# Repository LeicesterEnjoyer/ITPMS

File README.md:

# ITPMS

## A lightweight, energy-efficient **Improved TPMS with integrated tire wear assistant (ITPMS)**. Designed for universal compatibility and precision.

## 🔥 Key Features

- **🏋️ Ultra-Compact Design**  
    Minimal weight (<30g) ensures compatibility with most tires without affecting balance.

- **📡 Autonomous Operation**  
    Wakes up via accelerometer motion detection → close to none battery drain when stationary.

- **📊 Fast And Precise**  
    Uses device computing from sensors such as:
    - Pressure sensor
    - Temperature sensor (built into the MCU)
    - 3-axis accelerometer
    - Hall effect sensor

- **🔋 10-Year Battery Life**  
    Has low-powered elements and works only while the vehicle is moving.

- **🎯 Hall Effect Initialization**  
    Quick pairing with magnetic TPMS initializing pen.

## 🛠 How It Works

### Installation & Activation

1. **Open** remove the tire from the rim.
2. **Mount** the TPMs on the stem valve inside the tire .
3. **Wake & Pair** the TPMs with the magnetic TPMS initializing pen.
4. **Drive** to see the real time pressure and temperature changes.

### Data Transmission

| Trigger                                   | Action                         |
|-------------------------------------------|--------------------------------|
| > 5% pressure deviation from last read    | Instant RF alert to ECU        |
| > 5% temperature deviation from last read | Instant RF alert to ECU        |
| 10s without any significant changes       | Keep-alive ping                |

## 🔍 Code library

ITPMS/  
├── [Assistant/](Assistant/)&nbsp;&nbsp;&nbsp;&nbsp;&nbsp;&nbsp;&nbsp;&nbsp;&nbsp;&nbsp;&nbsp;&nbsp;&nbsp;&nbsp;&nbsp;&nbsp;&nbsp;&nbsp;&nbsp;&nbsp;&nbsp;&nbsp;&nbsp;&nbsp;&nbsp;&nbsp;&nbsp;&nbsp;&nbsp;&nbsp;&nbsp;&nbsp;# All files for the tire wear assistant.  
│&nbsp;&nbsp;&nbsp;├── [assets/](Assistant/assets/)&nbsp;&nbsp;&nbsp;&nbsp;&nbsp;&nbsp;&nbsp;&nbsp;&nbsp;&nbsp;&nbsp;&nbsp;&nbsp;&nbsp;&nbsp;&nbsp;&nbsp;&nbsp;&nbsp;&nbsp;&nbsp;&nbsp;&nbsp;&nbsp;&nbsp;&nbsp;&nbsp;&nbsp;&nbsp;&nbsp;&nbsp;# Assets for the UI.  
│&nbsp;&nbsp;&nbsp;├── [CSVhandling/](Assistant/CSVhandling/)  
│&nbsp;&nbsp;&nbsp;│&nbsp;&nbsp;&nbsp;&nbsp;|── [CSVmanager.py](Assistant/CSVhandling/CSVmanager.py)&nbsp;&nbsp;&nbsp;&nbsp;&nbsp;&nbsp;&nbsp;&nbsp;&nbsp;&nbsp;&nbsp;&nbsp;# Read and write operations for csv files.  
│&nbsp;&nbsp;&nbsp;│&nbsp;&nbsp;&nbsp;└── [DataGenerator.py](Assistant/CSVhandling/DataGenerator.py)&nbsp;&nbsp;&nbsp;&nbsp;&nbsp;&nbsp;&nbsp;&nbsp;# Generator for (TPMs) tire data.  
│&nbsp;&nbsp;&nbsp;│  
│&nbsp;&nbsp;&nbsp;├── [Data/](Assistant/Data/)&nbsp;&nbsp;&nbsp;&nbsp;&nbsp;&nbsp;&nbsp;&nbsp;&nbsp;&nbsp;&nbsp;&nbsp;&nbsp;&nbsp;&nbsp;&nbsp;&nbsp;&nbsp;&nbsp;&nbsp;&nbsp;&nbsp;&nbsp;&nbsp;&nbsp;&nbsp;&nbsp;&nbsp;&nbsp;&nbsp;&nbsp;&nbsp;# Data files for the different tire types and seasons.  
│&nbsp;&nbsp;&nbsp;├── [Tests/](Assistant/Tests/)&nbsp;&nbsp;&nbsp;&nbsp;&nbsp;&nbsp;&nbsp;&nbsp;&nbsp;&nbsp;&nbsp;&nbsp;&nbsp;&nbsp;&nbsp;&nbsp;&nbsp;&nbsp;&nbsp;&nbsp;&nbsp;&nbsp;&nbsp;&nbsp;&nbsp;&nbsp;&nbsp;&nbsp;&nbsp;&nbsp;&nbsp;&nbsp;# Tests for the functionalities of the TPMs classes.  
│&nbsp;&nbsp;&nbsp;├── [TPMsHandling/](Assistant/TPMsHandling/)  
│&nbsp;&nbsp;&nbsp;│&nbsp;&nbsp;&nbsp;&nbsp;|── [Tire.py](Assistant/TPMsHandling/Tire.py)&nbsp;&nbsp;&nbsp;&nbsp;&nbsp;&nbsp;&nbsp;&nbsp;&nbsp;&nbsp;&nbsp;&nbsp;&nbsp;&nbsp;&nbsp;&nbsp;&nbsp;&nbsp;&nbsp;&nbsp;&nbsp;&nbsp;&nbsp;&nbsp;&nbsp;&nbsp;# Represents the tire (TPMs).  
│&nbsp;&nbsp;&nbsp;│&nbsp;&nbsp;&nbsp;└── [Tires.py](Assistant/TPMsHandling/Tires.py)&nbsp;&nbsp;&nbsp;&nbsp;&nbsp;&nbsp;&nbsp;&nbsp;&nbsp;&nbsp;&nbsp;&nbsp;&nbsp;&nbsp;&nbsp;&nbsp;&nbsp;&nbsp;&nbsp;&nbsp;&nbsp;&nbsp;&nbsp;&nbsp;# Represents the tire complect of the vehicle.  
│&nbsp;&nbsp;&nbsp;│  
│&nbsp;&nbsp;&nbsp;├── [Main.py](Assistant/Main.py)&nbsp;&nbsp;&nbsp;&nbsp;&nbsp;&nbsp;&nbsp;&nbsp;&nbsp;&nbsp;&nbsp;&nbsp;&nbsp;&nbsp;&nbsp;&nbsp;&nbsp;&nbsp;&nbsp;&nbsp;&nbsp;&nbsp;&nbsp;&nbsp;&nbsp;&nbsp;&nbsp;&nbsp;# Runs the needed code and tests.  
│&nbsp;&nbsp;&nbsp;└── [TireAssistantGUI.py](Assistant/TireAssistantGUI.py)&nbsp;&nbsp;&nbsp;&nbsp;&nbsp;&nbsp;&nbsp;&nbsp;&nbsp;&nbsp;# UI for the assistant. (*Run the file to start it.)  
│  
├── [CAD/](CAD/)&nbsp;&nbsp;&nbsp;&nbsp;&nbsp;&nbsp;&nbsp;&nbsp;&nbsp;&nbsp;&nbsp;&nbsp;&nbsp;&nbsp;&nbsp;&nbsp;&nbsp;&nbsp;&nbsp;&nbsp;&nbsp;&nbsp;&nbsp;&nbsp;&nbsp;&nbsp;&nbsp;&nbsp;&nbsp;&nbsp;&nbsp;&nbsp;&nbsp;&nbsp;&nbsp;&nbsp;&nbsp;&nbsp;# KiCad models of the pcb.  
├── [Datasheets/](Datasheets/)&nbsp;&nbsp;&nbsp;&nbsp;&nbsp;&nbsp;&nbsp;&nbsp;&nbsp;&nbsp;&nbsp;&nbsp;&nbsp;&nbsp;&nbsp;&nbsp;&nbsp;&nbsp;&nbsp;&nbsp;&nbsp;&nbsp;&nbsp;&nbsp;&nbsp;&nbsp;&nbsp;# Datasheets of all components used in the pcb.  
├── [TPMS&TPMs/](TPMS&TPMs/)&nbsp;&nbsp;&nbsp;&nbsp;&nbsp;&nbsp;&nbsp;&nbsp;&nbsp;&nbsp;&nbsp;&nbsp;&nbsp;&nbsp;&nbsp;&nbsp;&nbsp;&nbsp;&nbsp;&nbsp;&nbsp;&nbsp;&nbsp;&nbsp;# All files and libraries used by the hardware.  
│&nbsp;&nbsp;&nbsp;├── [Code](TPMS&TPMs/Code/)/  
│&nbsp;&nbsp;&nbsp;│&nbsp;&nbsp;&nbsp;&nbsp;|── [Receiver.ino](TPMS&TPMs/Code/Receiver.ino)&nbsp;&nbsp;&nbsp;&nbsp;&nbsp;&nbsp;&nbsp;&nbsp;&nbsp;&nbsp;&nbsp;&nbsp;&nbsp;&nbsp;&nbsp;&nbsp;&nbsp;# Receiver algorithm.  
│&nbsp;&nbsp;&nbsp;│&nbsp;&nbsp;&nbsp;└── [Transmitter.ino](TPMS&TPMs/Code/Transmitter.ino)&nbsp;&nbsp;&nbsp;&nbsp;&nbsp;&nbsp;&nbsp;&nbsp;&nbsp;&nbsp;&nbsp;&nbsp;# Transmitter algorithm.  
│&nbsp;&nbsp;&nbsp;├── [Libraries/](TPMS&TPMs/Libraries/)  
│&nbsp;&nbsp;&nbsp;│&nbsp;&nbsp;&nbsp;&nbsp;├── [Receiver/](TPMS&TPMs/Libraries/Receiver/)&nbsp;&nbsp;&nbsp;&nbsp;&nbsp;&nbsp;&nbsp;&nbsp;&nbsp;&nbsp;&nbsp;&nbsp;&nbsp;&nbsp;&nbsp;&nbsp;&nbsp;&nbsp;&nbsp;&nbsp;# Receiver libraries.  
│&nbsp;&nbsp;&nbsp;│&nbsp;&nbsp;&nbsp;&nbsp;├── [TPMs/](TPMS&TPMs/Libraries/TPMs/)&nbsp;&nbsp;&nbsp;&nbsp;&nbsp;&nbsp;&nbsp;&nbsp;&nbsp;&nbsp;&nbsp;&nbsp;&nbsp;&nbsp;&nbsp;&nbsp;&nbsp;&nbsp;&nbsp;&nbsp;&nbsp;&nbsp;&nbsp;&nbsp;# Transmitter libraries.  
│&nbsp;&nbsp;&nbsp;│&nbsp;&nbsp;&nbsp;&nbsp;└── [TPMS_structures.h](TPMS&TPMs/Libraries/TPMS_structures.h)&nbsp;&nbsp;&nbsp;&nbsp;&nbsp;# Common configuration.  
│  
├── [LICENSE](LICENSE)  
├── [README.md](README.md)&nbsp;&nbsp;&nbsp;&nbsp;&nbsp;&nbsp;&nbsp;&nbsp;&nbsp;&nbsp;&nbsp;&nbsp;&nbsp;&nbsp;&nbsp;&nbsp;&nbsp;&nbsp;&nbsp;&nbsp;&nbsp;&nbsp;&nbsp;&nbsp;&nbsp;&nbsp;# You're here!  
└── [requirements.txt](requirements.txt)&nbsp;&nbsp;&nbsp;&nbsp;&nbsp;&nbsp;&nbsp;&nbsp;&nbsp;&nbsp;&nbsp;&nbsp;&nbsp;&nbsp;&nbsp;&nbsp;&nbsp;&nbsp;&nbsp;&nbsp;# Python dependencies.  

## 🔑 Setup

### Assistant

Run this command to download the needed dependencies:
```sh
pip install -r .requirements.txt
```
After that you can run the UI with:
```sh
python Assistant/TireAssistantGUI.py
```

### TPMS & TPMs

The software must be flashed on a special TPMs via SPI programmer. From there you have to follow the steps in [Installation & Activation](#installation--activation) an you will be ready to use it.

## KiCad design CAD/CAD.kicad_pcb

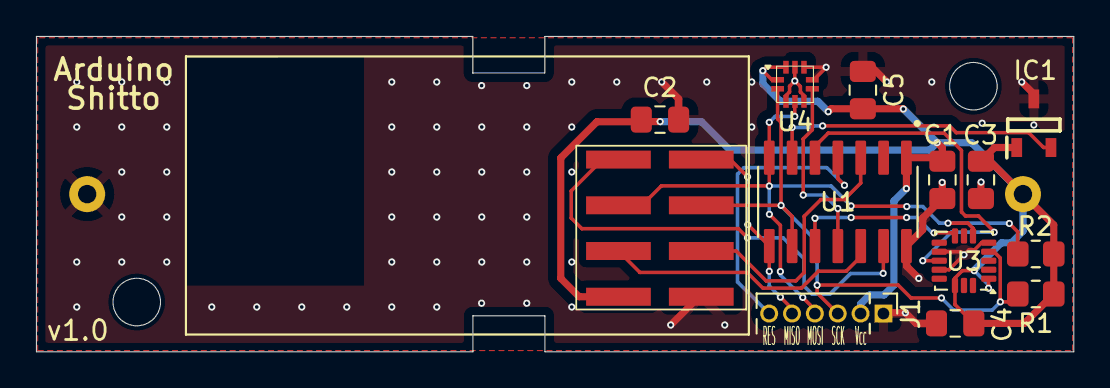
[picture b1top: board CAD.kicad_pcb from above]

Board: 2 copper layers, 57.6 x 17.5 mm, 14 parts (1 on the bottom side), 13 nets.

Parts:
BT1: 2460; BAT_2460
C1, C3, C4, C5: 100nF; C_0805_2012Metric_Pad1.18x1.45mm_HandSolder
C2: 10µF; C_0805_2012Metric_Pad1.18x1.45mm_HandSolder
IC1: Si7201-B-04-IV; SOT95P275X125-3N
J1: Conn_01x06_Pin; PinHeader_1x06_P1.27mm_Vertical
R1, R2: 10kΩ; R_0805_2012Metric_Pad1.20x1.40mm_HandSolder
U1: ATTINY84-20SSU; SOIC127P600X175-14N
U2: NRF24L01_Breakout; nRF24L01_Breakout
U3: LIS3DH; LGA-16_3x3mm_P0.5mm_LayoutBorder3x5y
U4: ILPS22QS; ILPS22QSTR

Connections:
3.6V: BT1.P, C1.2, C2.2, C3.2, C4.2, C5.2, IC1.1 (VDD), J1.2, R1.1, R2.1, U1.1 (VCC), U2.2 (VCC), U3.1 (VDD_IO), U3.14 (VDD), U4.1 (Vdd_IO), U4.10 (Vdd)
/CE: U1.3 (PB1), U2.3 (CE)
/CS/A: U1.10 (PA3), U3.8 (CS)
/CS/P: U1.11 (PA2), U4.6 (CS)
/CS/RF: U1.12 (PA1), U2.4 (~CSN)
/INT_ACC: U1.5 (PB2), U3.11 (INT1)
/INT_HALL: IC1.2 (OUT1), U1.6 (PA7)
/IRQ: U1.13 (PA0), U2.8 (IRQ)
/MISO: J1.5, U1.8 (PA5), U2.7 (MISO)
/MOSI: J1.4, R2.2, U1.7 (PA6), U2.6 (MOSI), U3.6 (SDI), U4.4 (SDA)
/RESET: J1.6, U1.4 (PB3)
/SCK: J1.3, R1.2, U1.9 (PA4), U2.5 (SCK), U3.4 (SPC), U4.2 (SCK)
GND: BT1.N, C1.1, C2.1, C3.1, C4.1, C5.1, IC1.3 (GND), J1.1, U1.14 (GND), U2.1 (GND), U3.5 (GND), U3.10 (GND), U3.12 (GND), U4.3 (RES), U4.5 (AH2/QVAR2), U4.7 (AH1/QVAR1), U4.8 (GND_IO), U4.9 (GND)

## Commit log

2024-12-08 Datasheets
2024-12-08 KiCad project
2024-12-08 Generated GUI by Tkinter Designer
2024-12-08 Tire class for TPMs data handling + unit tests
2024-12-09 Fixed condition (int -> float)
2024-12-09 Tires class for TPMs data handling + unit tests
2024-12-09 CSV handling
2024-12-12 Small changes
2024-12-12 GUI functionalities
2024-12-12 Tha average daily drive time is now an input
2025-01-30 Moved the assistant code in separate directory
2025-01-30 Moved the Main and TireAssistantGUI files too
2025-02-03 TPMs and receiver algorithms
2025-02-04 README and requirements
2025-02-04 Sleep TPMs when necessary
2025-02-05 Cosmetic changes
2025-02-24 Correction of inaccuracies
